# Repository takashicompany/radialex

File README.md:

# Radialex

Radialex(ラディアレックス)は一体型の40%のキーボードです。  
放射状に規則的に配置されたキーレイアウトは手を自然な体勢のまま置くことができ、ホームポジションから最短距離で文字を打つことを可能としています。  
キーボードの中央部にはシンボルとしてのキーやキーキャップを配置することができ、またバックライトLEDによるライトアップがされます。  
オプションでMXソケットによるキースイッチの取り替えや、LED、コンスルーにも対応しており、使用するスタイルにあわせた組み立てが可能です。  
また、ファームウェアがVIA(Remap)に対応しているため、Webブラウザからキーマップを書き換えることが可能です。

## Store
- [遊舎工房](https://shop.yushakobo.jp/products/3350)
- [Booth](https://takashicompany.booth.pm/items/3394593)

## ガーバーデータ、ケースのデータについて
ご自由にご利用ください。  
尚、ガーバーデータとケースのデータをご自身で利用された際に発生した不都合に関しての責任は負いかねます。

### ガーバーデータやケースを利用した例

[@morecat_lab
](https://twitter.com/morecat_lab)さんの[3Dプリンター製のケース](https://github.com/kuwatay/radialex-3dprint-case)  

## 必要な部品

### キットに同梱されているもの
|部品|個数|備考|
|:--|:--|:--|
|PCB|1|リードタイプと表面実装のダイオードに対応。|
|トッププレート|1||
|ボトムプレート|1||
|中央トッププレート|1||
|中央積層プレート|1||
|表面実装ダイオード|45||
|m2スペーサー(シルバー5mm)|8||
|m2ネジ(シルバー4mm)|8||
|m2ネジ(シルバー8mm)|4||
|m2ネジ(ゴールド18mm)4||
|リセットスイッチ|1||
|キースイッチソケットMX用|1||
|滑り止めシール|6||

### 別途用意するもの
|部品|個数|備考|
|:--|:--|:--|
|キースイッチ|45|Cherry MX互換のもの。|
|キーキャップ|45|全て1u。Chery MX互換のもの。|
|Pro Micro|1||
|USBケーブル|1|Pro MicroとPCを接続します。|

### オプション
|部品|個数|備考|
|:--|:--|:--|
|コンスルー|2|12pin、13pinに対応しておりますのでMCU(Pro Micro)にあわせて選択が可能です。|
|MXソケット|44|中央のキー以外は、キースイッチのはんだ付け/MXソケットによる挿し込みの両方に対応。|
|LED(SK6812MINI-E)|2|中央のキーとキーボード手前側の穴をバックライトで光らせることができます。|
|LED(WS2812B)|10|アンダーグロウライトとしてキーボードの底面を光らせることができます。|

## 組みたて方

[Rev1の組み立て方はこちら](https://github.com/takashicompany/radialex/blob/master/build_rev1.md)

見分け方 : Rev1はPro Microを底面側に取り付けるため、ボトムプレートに切り抜きがあります。  

Rev2以降の組み立て方は以下になります。

### 1. PCBの表裏を確認する

表  

裏  

### 2. ダイオードをはんだづけする

プリントにあわせてダイオードの向き(端に黒線がついているもの)を確認します。  
スルーホール型のダイオード、表面実装型のダイオードの両方に対応しております。

#### スルーホール型のダイオードの場合

ダイオードを穴に通るように折り曲げます。  

はんだ付けを行います。  

ニッパーで足を切る際は、可能な限り平坦になるようにすると後の作業が楽に進めます。  

全部で45箇所となります。  

#### 表面実装型のダイオードの場合

表面実装型のダイオードを使用する場合は表面にはんだが漏れないようにマスキングテープで塞ぎます。  

表面実装型ダイオードのはんだ付けは以下の動画を参考にすると良いかと思います。(PCBが別のキーボードになっておりますが、ご了承ください). 

https://user-images.githubusercontent.com/4215759/126895350-43ae4cd4-408b-4ff4-ab5c-2903e0420978.mov

PCBのダイオードのはんだづけ箇所の片方にはんだを乗せておき(予備はんだ)、ピンセットでダイオードを持ちながら予備はんだを溶かしながらダイオードをはんだづけします。  
片方のはんだづけが終わったら、動画と同じく反対側をはんだづけしましょう。

全部で45箇所となります。  

### 3. 中央のキーのMXソケットの取り付け

中央のキーのみMXソケットでキースイッチを固定します。  

MXソケット  

MXソケットのはんだ付け部分の片方に事前にはんだを載せておきます。  

ピンセットでMXソケットを抑えながら事前に載せたはんだを溶かしながらMXソケットとPCBをはんだ付けします  

もう片方もはんだ付けを行います。  

### 4. リセットスイッチの取り付け

リセットスイッチの取り付け場所はPCBの裏面中央のやや手前側です。  

リセットスイッチがPCBの裏面から押せるように穴に通します。  

表面からはんだ付けを行います。この際、可能な限り平坦になるようにニッパーで切ると後の作業がスムーズに行えます。  

### 5. トッププレートとキースイッチの取り付け

トッププレートやボトムプレート、中央プレートはアクリルの保護シートが貼ってるので、組み立てる際に剥がしてください。  

製造の工程上、模様が発生している可能性がありますが、ご理解いただけますと幸いです。  

PCBにトッププレートを載せます。  

トッププレートにキースイッチを取り付け、はんだ付けもしくはMXソケットへの差し込みを行います。  

### 6. Pro Microの取り付け

Pro Microを取り付けます。  
PCBはコンスルーに対応しております。  

Pro Microの取り付け位置を確認します。  

PCBにピンヘッダ(又はコンスルー)を取り付けます。  
穴は13個ありますが、Pro Microの取り付け穴は12個なので、1つ余ります。  
Pro Microの印字とPCBの印字が合うように挿してください。  

ピンヘッダ(コンスルー)にPro Microを挿してはんだ付けをします。  

ピンの余った部分はニッパーで切ります。    

ピンヘッダの場合は裏面からはんだ付けを行います。  
(コンスルーの場合は、PCBとのはんだ付けをしなくて大丈夫です)

### 7. 中央プレートの取り付け

中央プレートは二種類あります。  

18mmのネジとスペーサーを用います。  

PCBの裏側から、スペーサーでネジと中央プレートを取り付けます。  

表面は下図のようになります。  

### 8. ファームウェアの用意と確認

[Remap](https://remap-keys.app/catalog/IxsMPjShxAP0NbiQGbKQ/firmware)からVIAのファームウェアを書き込むことが可能です。  

Remapの使い方は[千葉千夏/あずさんの記事](https://note.com/azulee/n/n8557fdfbc679#MkVkQ)で説明されております。

ファームウェアのソースコードは[こちら](https://github.com/qmk/qmk_firmware/pull/14949)です。

VIAのファームウェアを書き込んだ状態で[Remap](https://remap-keys.app/)からキーマップを変更できます。  

### 9. LEDの取り付け(オプション)

Radialexでは、2種類のLEDを搭載できます。  
1-2番はバックライト(SK6812MINI-E)、3番から12番まではアンダーグロウ(WS2812B)となります。  

バックライトのLEDを付ける際はシルクで塗られたところにGND(LEDの角が欠けている部分)が来るように配置します。  
事前にはんだを乗せておくのが良いです。  

4箇所をはんだ付けします。  

中央のキースイッチと手前の穴が光ります。  

アンダーグロウも同様に、シルクの三角の部分にGND(LEDが角が欠けている部分)が来るように配置します。  

同じく4箇所をはんだ付けします。  

12箇所が光るかを確認します。  

### 10. ボトムプレートの取り付け

最後にボトムプレートを取り付けます。  

トッププレート側は8mmのネジ、ボトムプレート側は4mmのネジでスペーサーを赤丸の位置に留めます。  

ボトムプレートを取り付けたら滑り止めシールを底面に取り付けます。

赤丸の位置に貼るとグラつきが少ないです。  

### 11. キーキャップを取り付ける

最後にキーキャップを取り付けて完成です。  

### 12. 自慢する
完成しましたら、ぜひSNSなどに写真を投稿頂ければと思います。  
Twitterのハッシュタグは`#Radialex`を付けていただけば幸いです。  
キットを組み立てた感想や、キーボードを使った所感などをお待ちしております！  

また、毎週日曜日の１9時より実施されている[#KEEP_PD](https://twitter.com/hashtag/KEEB_PD?f=live)に投稿頂くこともオススメです。  
開催の告知は[@KEEB_PD](https://twitter.com/KEEB_PD)にて行われております。

ご不明な点などございましたら、[@takashicompany](https://twitter.com/takashicompany)にメンションやDM頂ければと思います！

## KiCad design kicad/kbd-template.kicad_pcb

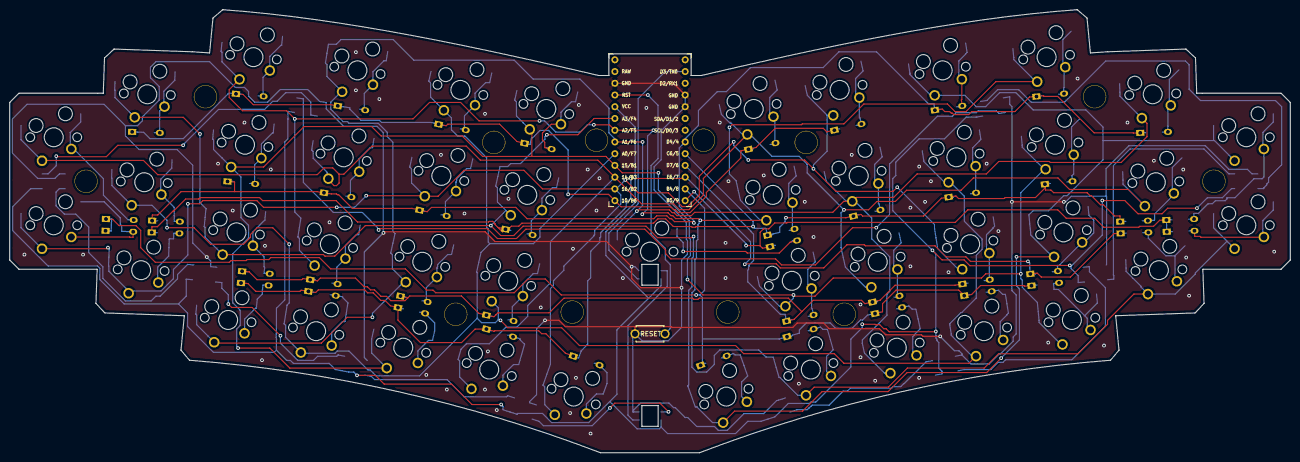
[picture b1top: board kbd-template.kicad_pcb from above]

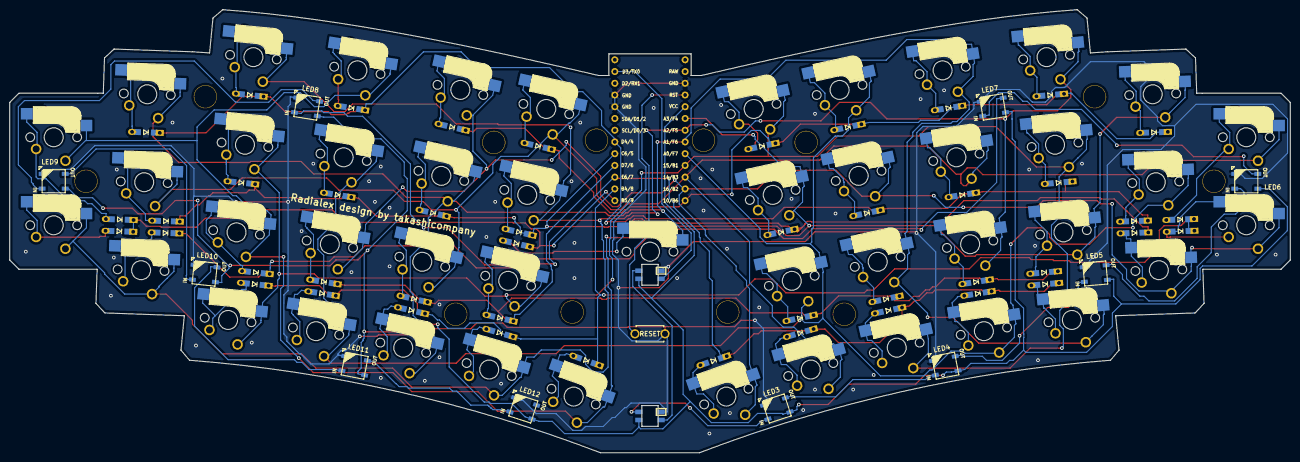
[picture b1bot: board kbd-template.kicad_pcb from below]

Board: 2 copper layers, 277.2 x 95.9 mm, 116 parts (56 on the bottom side), 74 nets.

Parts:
D1, D2, D3, D4, D5, D6, D7, D8, D9, D10, D11, D12, D13, D14, D15, D16, D17, D18, D19, D20, D21, D22, D23, D24, D25, D26, D27, D28, D29, D30, D31, D32, D33, D34, D35, D36, D37, D38, D39, D40, D41, D42, D43, D44, D45: DIODE; D3_TH_SMD_v2
Hole01, Hole02, Hole03, Hole04, Hole05, Hole06, Hole07, Hole08, Hole09, Hole10, Hole11, Hole12: Val**; HOLE
LED1, LED2: YS-SK6812MINI-E; SK6812MINI_bg
LED3, LED4, LED5, LED6, LED7, LED8, LED9, LED10, LED11, LED12: WS2812B
RESET_SW1: SW_Push; ResetSW
SW1, SW2, SW3, SW4, SW5, SW6, SW7, SW8, SW9, SW10, SW11, SW12, SW13, SW14, SW15, SW16, SW17, SW18, SW19, SW20, SW21, SW22, SW23, SW24, SW25, SW26, SW27, SW28, SW29, SW30, SW31, SW32, SW33, SW34, SW35, SW36, SW37, SW38, SW39, SW40, SW41, SW42, SW43, SW44: SW_Push; CherryMX_TH-Hotswap
SW45: SW_Push; CherryMX_Hotswap
U1: ProMicro; ProMicro_v3.5_13pin_print-inside

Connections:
GND: LED1.3, LED2.3, LED3.3, LED4.3, LED5.3, LED6.3, LED7.3, LED8.3, LED9.3, LED10.3, LED11.3, LED12.3, RESET_SW1.2, U1.3, U1.4, U1.23
unnamed: D1.2, SW1.2
unnamed: D2.2, SW2.2
unnamed: D3.2, SW3.2
unnamed: D4.2, SW4.2
unnamed: D5.2, SW5.2
unnamed: D6.2, SW6.2
unnamed: D7.2, SW7.2
unnamed: D8.2, SW8.2
unnamed: D9.2, SW9.2
unnamed: D10.2, SW10.2
unnamed: D11.2, SW11.2
unnamed: D12.2, SW12.2
unnamed: D13.2, SW13.2
unnamed: D14.2, SW14.2
unnamed: D15.2, SW15.2
unnamed: D16.2, SW16.2
unnamed: D17.2, SW17.2
unnamed: D18.2, SW18.2
unnamed: D19.2, SW19.2
unnamed: D20.2, SW20.2
unnamed: D21.2, SW21.2
unnamed: D22.2, SW22.2
unnamed: D23.2, SW23.2
unnamed: D24.2, SW24.2
unnamed: D25.2, SW25.2
unnamed: D26.2, SW26.2
unnamed: D27.2, SW27.2
unnamed: D28.2, SW28.2
unnamed: D29.2, SW29.2
unnamed: D30.2, SW30.2
unnamed: D31.2, SW31.2
unnamed: D32.2, SW32.2
unnamed: D33.2, SW33.2
unnamed: D34.2, SW34.2
unnamed: D35.2, SW35.2
unnamed: D36.2, SW36.2
unnamed: D37.2, SW37.2
unnamed: D38.2, SW38.2
unnamed: D39.2, SW39.2
unnamed: D40.2, SW40.2
unnamed: D41.2, SW41.2
unnamed: D42.2, SW42.2
unnamed: D43.2, SW43.2
unnamed: D44.2, SW44.2
unnamed: D45.2, SW45.2
unnamed: LED1.2, LED2.4
unnamed: LED2.2, LED3.4
unnamed: LED3.2, LED4.4
unnamed: LED4.2, LED5.4
unnamed: LED5.2, LED6.4
unnamed: LED6.2, LED7.4
unnamed: LED7.2, LED8.4
unnamed: LED8.2, LED9.4
unnamed: LED10.2, LED11.4
unnamed: LED9.2, LED10.4
unnamed: LED11.2, LED12.4
VCC: LED1.1, LED2.1, LED3.1, LED4.1, LED5.1, LED6.1, LED7.1, LED8.1, LED9.1, LED10.1, LED11.1, LED12.1, U1.21
col1: SW1.1, SW8.1, SW15.1, SW22.1, SW29.1, SW36.1, SW43.1, U1.20
col2: SW2.1, SW9.1, SW16.1, SW23.1, SW30.1, SW37.1, SW44.1, U1.19
col3: SW3.1, SW10.1, SW17.1, SW24.1, SW31.1, SW38.1, SW45.1, U1.18
col4: SW4.1, SW11.1, SW18.1, SW25.1, SW32.1, SW39.1, U1.17
col5: SW5.1, SW12.1, SW19.1, SW26.1, SW33.1, SW40.1, U1.16
col6: SW6.1, SW13.1, SW20.1, SW27.1, SW34.1, SW41.1, U1.15
col7: SW7.1, SW14.1, SW21.1, SW28.1, SW35.1, SW42.1, U1.14
led: LED1.4, U1.1
reset: RESET_SW1.1, U1.22
row1: D1.1, D2.1, D3.1, D4.1, D5.1, D6.1, D7.1, U1.13
row2: D8.1, D9.1, D10.1, D11.1, D12.1, D13.1, D14.1, U1.7
row3: D15.1, D16.1, D17.1, D18.1, D19.1, D20.1, D21.1, U1.8
row4: D22.1, D23.1, D24.1, D25.1, D26.1, D27.1, D28.1, U1.9
row5: D29.1, D30.1, D31.1, D32.1, D33.1, D34.1, D35.1, U1.10
row6: D36.1, D37.1, D38.1, D39.1, D40.1, D41.1, D42.1, U1.11
row7: D43.1, D44.1, D45.1, U1.12

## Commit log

2021-10-25 画像を追加
2021-10-29 一旦コミット
2021-10-29 さらに追加
2021-10-29 画像を載せた
2021-10-30 ちょっと修正
2021-10-30 モノを書いた。
2021-10-30 同梱物を確認
2021-11-02 コンスルーの個数を修正
2021-12-06 rev1とrev2
2021-12-06 リンク先に組み立て方を記載
2021-12-16 リネーム
2022-01-09 誤字を修正
2022-02-24 ダイオードを修正
2022-03-01 写真を追加
2022-04-29 データーを追加
2022-05-03 LED穴のボトムプレート
2022-05-03 ボトムプレートにバリエーションを追加
2022-05-03 ケースを更新
2022-05-10 画像を更新
2022-05-31 遊舎工房のアクリルカットサービスで使ったデータ
2022-07-23 遊舎工房 A4 3mm
2022-09-03 使ってないデータを削除
2022-09-11 ケースに余計なデータ入ってたので消す
2022-09-11 40mm ロゴ
2024-05-22 kicad
